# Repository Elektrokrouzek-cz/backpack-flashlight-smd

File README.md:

# Backpack flashlight - SMD
This is the construction of backpack flashlight with SMD components. It is based on ATTINY24A microcontroller.

PCB is 2-layer and was designed using KiCad 9. Fabrication output for JLCPCB is in gerber folder.

Happy soldering!

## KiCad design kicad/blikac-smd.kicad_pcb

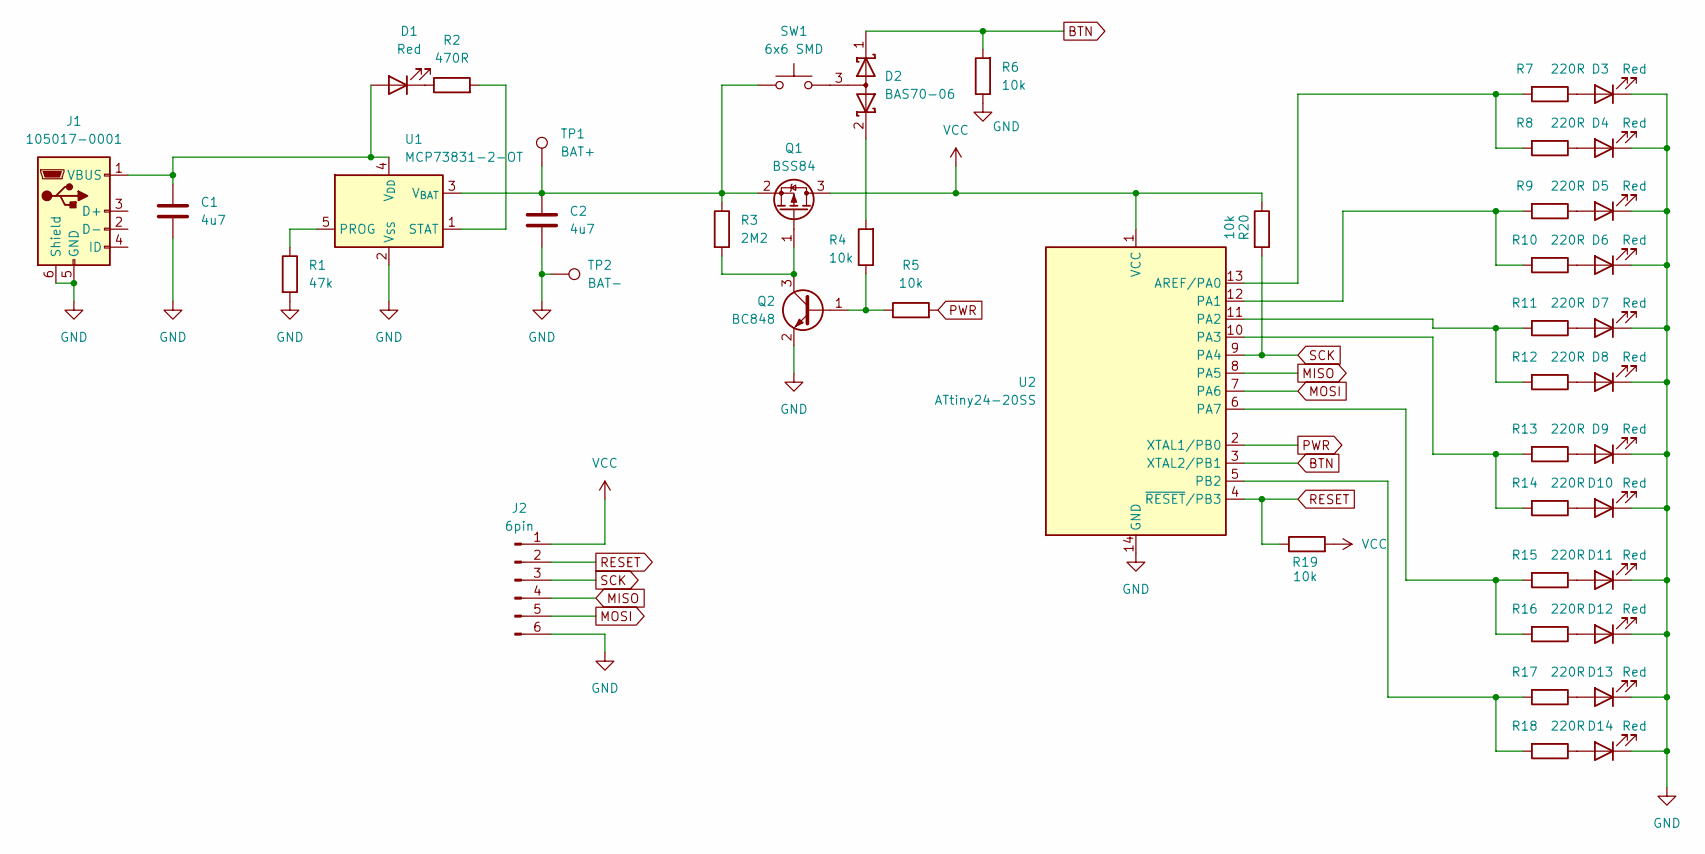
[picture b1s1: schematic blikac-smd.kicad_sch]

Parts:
C1, C2: 4u7; C_1206_3216Metric_Pad1.33x1.80mm_HandSolder
D1, D3, D4, D5, D6, D7, D8, D9, D10, D11, D12, D13, D14: Red; LED_1206_3216Metric_Pad1.42x1.75mm_HandSolder
D2: BAS70-06; SOT-23_Handsoldering
J1: 105017-0001; USB_Micro-B_Molex-105017-0001
J2: 6pin; PinHeader_1x06_P2.54mm_Vertical
Q1: BSS84; SOT-23_Handsoldering
Q2: BC848; SOT-23_Handsoldering
R1: 47k; R_1206_3216Metric_Pad1.30x1.75mm_HandSolder
R2: 470R; R_1206_3216Metric_Pad1.30x1.75mm_HandSolder
R3: 2M2; R_1206_3216Metric_Pad1.30x1.75mm_HandSolder
R4, R5, R6, R19, R20: 10k; R_1206_3216Metric_Pad1.30x1.75mm_HandSolder
R7, R8, R9, R10, R11, R12, R13, R14, R15, R16, R17, R18: 220R; R_1206_3216Metric_Pad1.30x1.75mm_HandSolder
SW1: 6x6 SMD; SW_SPST_PTS645
TP1: BAT+; TestPoint_THTPad_2.0x2.0mm_Drill1.0mm
TP2: BAT-; TestPoint_THTPad_2.0x2.0mm_Drill1.0mm
U1: MCP73831-2-OT; SOT-23-5
U2: ATtiny24-20SS; SOIC-14_3.9x8.7mm_P1.27mm

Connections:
BTN: D2.1 (K), R6.2, U2.3 (XTAL2/PB1)
GND: C1.2, C2.2, D3.1 (K), D4.1 (K), D5.1 (K), D6.1 (K), D7.1 (K), D8.1 (K), D9.1 (K), D10.1 (K), D11.1 (K), D12.1 (K), D13.1 (K), D14.1 (K), J1.5 (GND), J1.6 (Shield), J2.6, Q2.2 (E), R1.2, R6.1, TP2.1, U1.2 (V_{SS}), U2.14 (GND)
MISO: J2.4, U2.8 (PA5)
MOSI: J2.5, U2.7 (PA6)
unnamed: C1.1, D1.2 (A), J1.1 (VBUS), U1.4 (V_{DD})
unnamed: D1.1 (K), R2.1
unnamed: D2.3 (A), SW1.2
unnamed: D2.2 (K), R4.2
unnamed: D3.2 (A), R7.1
unnamed: D4.2 (A), R8.1
unnamed: D5.2 (A), R9.1
unnamed: D6.2 (A), R10.1
unnamed: D7.2 (A), R11.1
unnamed: D8.2 (A), R12.1
unnamed: D9.2 (A), R13.1
unnamed: D10.2 (A), R14.1
unnamed: D11.2 (A), R15.1
unnamed: D12.2 (A), R16.1
unnamed: D13.2 (A), R17.1
unnamed: D14.2 (A), R18.1
unnamed: Q1.1 (G), Q2.3 (C), R3.2
unnamed: C2.1, Q1.2 (S), R3.1, SW1.1, TP1.1, U1.3 (V_{BAT})
unnamed: Q2.1 (B), R4.1, R5.1
unnamed: R1.1, U1.5 (PROG)
unnamed: R2.2, U1.1 (STAT)
unnamed: R7.2, R8.2, U2.13 (AREF/PA0)
unnamed: R9.2, R10.2, U2.12 (PA1)
unnamed: R11.2, R12.2, U2.11 (PA2)
unnamed: R13.2, R14.2, U2.10 (PA3)
unnamed: R15.2, R16.2, U2.6 (PA7)
unnamed: R17.2, R18.2, U2.5 (PB2)
PWR: R5.2, U2.2 (XTAL1/PB0)
RESET: J2.2, R19.1, U2.4 (~RESET/PB3)
SCK: J2.3, R20.2, U2.9 (PA4)
VCC: J2.1, Q1.3 (D), R19.2, R20.1, U2.1 (VCC)

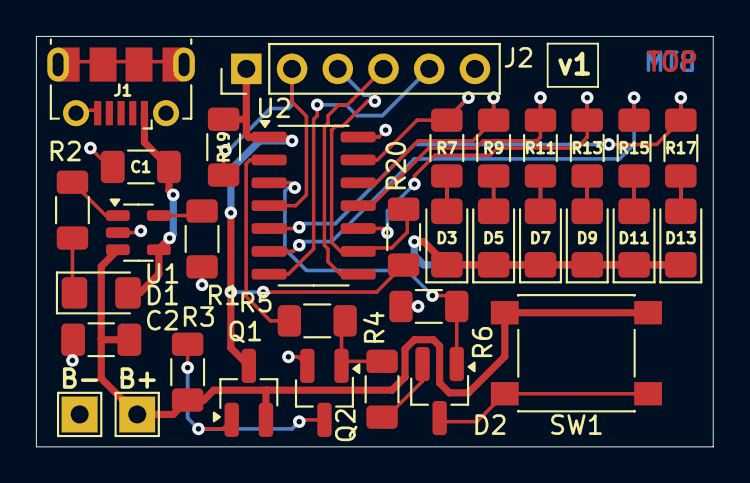
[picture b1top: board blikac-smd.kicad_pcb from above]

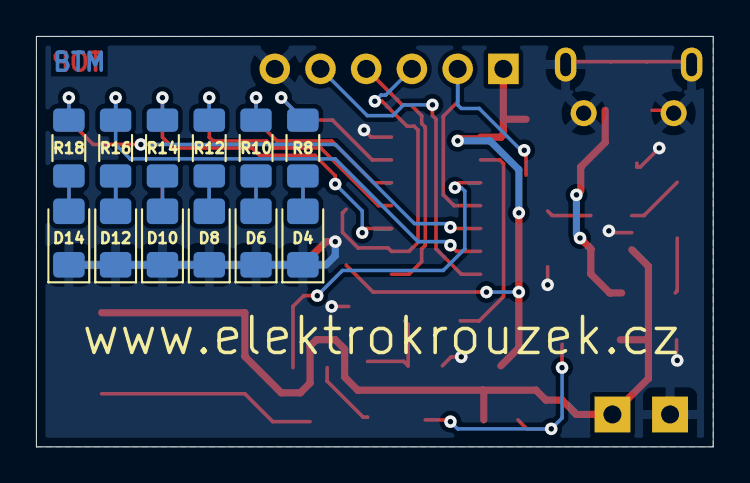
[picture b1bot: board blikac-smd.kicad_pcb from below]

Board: 2 copper layers, 37.6 x 22.8 mm, 45 parts (12 on the bottom side), 35 nets.

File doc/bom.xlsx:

Reference | Value | Qty
C1,C2 | 4u7 | 2
D1,D3,D4,D5,D6,D7,D8,D9,D10,D11,D12,D13,D14 | 1206 Red | 13
D2 | BAS70-06 | 1
J1 | 105017-0001 | 1
J2 | 6pin | 1
Q1 | BSS84 | 1
Q2 | BC848 | 1
R1 | 47k | 1
R2 | 470R | 1
R3 | 2M2 | 1
R4,R5,R6,R19,R20 | 10k | 5
R7,R8,R9,R10,R11,R12,R13,R14,R15,R16,R17,R18 | 220R | 12
SW1 | 6x6 SMD | 1
TP1 | BAT+ | 1
TP2 | BAT- | 1
U1 | MCP73831-2-OT | 1
U2 | ATtiny24-20SS | 1

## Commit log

2025-11-05 Manual update, 3D models, construction brief
2025-11-05 BOM update
